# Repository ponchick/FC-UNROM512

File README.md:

# FC-UNROM512

UNROM512 Famicom cartridge PCB (UNROM/UOROM family, extended PRG-ROM bank switching).

Russian version: [`README.ru.md`](README.ru.md)

More details about UNROM512 format and compatibility:

- [NESdev Wiki - UNROM 512](https://www.nesdev.org/wiki/UNROM_512)
- [NESdev Wiki mirror - UNROM 512](https://nesdev-wiki.nes.science/wikipages/UNROM_512.xhtml)

---

## Jumpers (board configuration)

### 1) Flash memory mode (write protection / self-flashing)

| Configuration | `FLASHLOCKED1`-`FLASHLOCKED4` | `FLASHABLE` | 74*139 | Bus conflicts |
| :--- | :---: | :---: | :---: | :---: |
| **Not Flashable** (write-protected) | Closed | Open | Not installed | **Present** |
| **Flashable** (self-flashable) | Open | Closed | Installed | **Absent** |

---

### 2) Mirroring

**Mirroring must match the ROM you are programming.** The game expects a specific mode (vertical/horizontal/1-screen). A wrong setting causes visual glitches.

Only one of these jumpers should be closed. For **Vertical mirroring**, close `VERTICAL` and keep `HORIZONTAL` and `ONE` open.

---

### 3) CHR RAM size configuration (8/16/32 KiB)

**The actual CHR RAM size is defined by the physical RAM chip** (for example, 62256 = 32 KiB). Jumpers only route the required address lines.

| Size | `CHR RAM 8k` | `CHR RAM 8k/16k` | `CHR RAM 16k/32k` | `CHR RAM 32k` |
| :--- | :---: | :---: | :---: | :---: |
| 8 KiB | Closed | Closed | Open | Open |
| 16 KiB | Open | Closed | Closed | Open |
| 32 KiB | Open | Open | Closed | Closed |

> **Use smaller CHR RAM sizes (8/16 KiB) only if the target ROM explicitly supports them.** Most UNROM512 / Mapper 30 software expects 32 KiB. Forcing a smaller size on unsupported ROMs can cause errors.

---

## License

This project is licensed under CERN Open Hardware Licence Version 2 - Permissive (`CERN-OHL-P-2.0`), see `LICENSE`.

SPDX-License-Identifier: `CERN-OHL-P-2.0`

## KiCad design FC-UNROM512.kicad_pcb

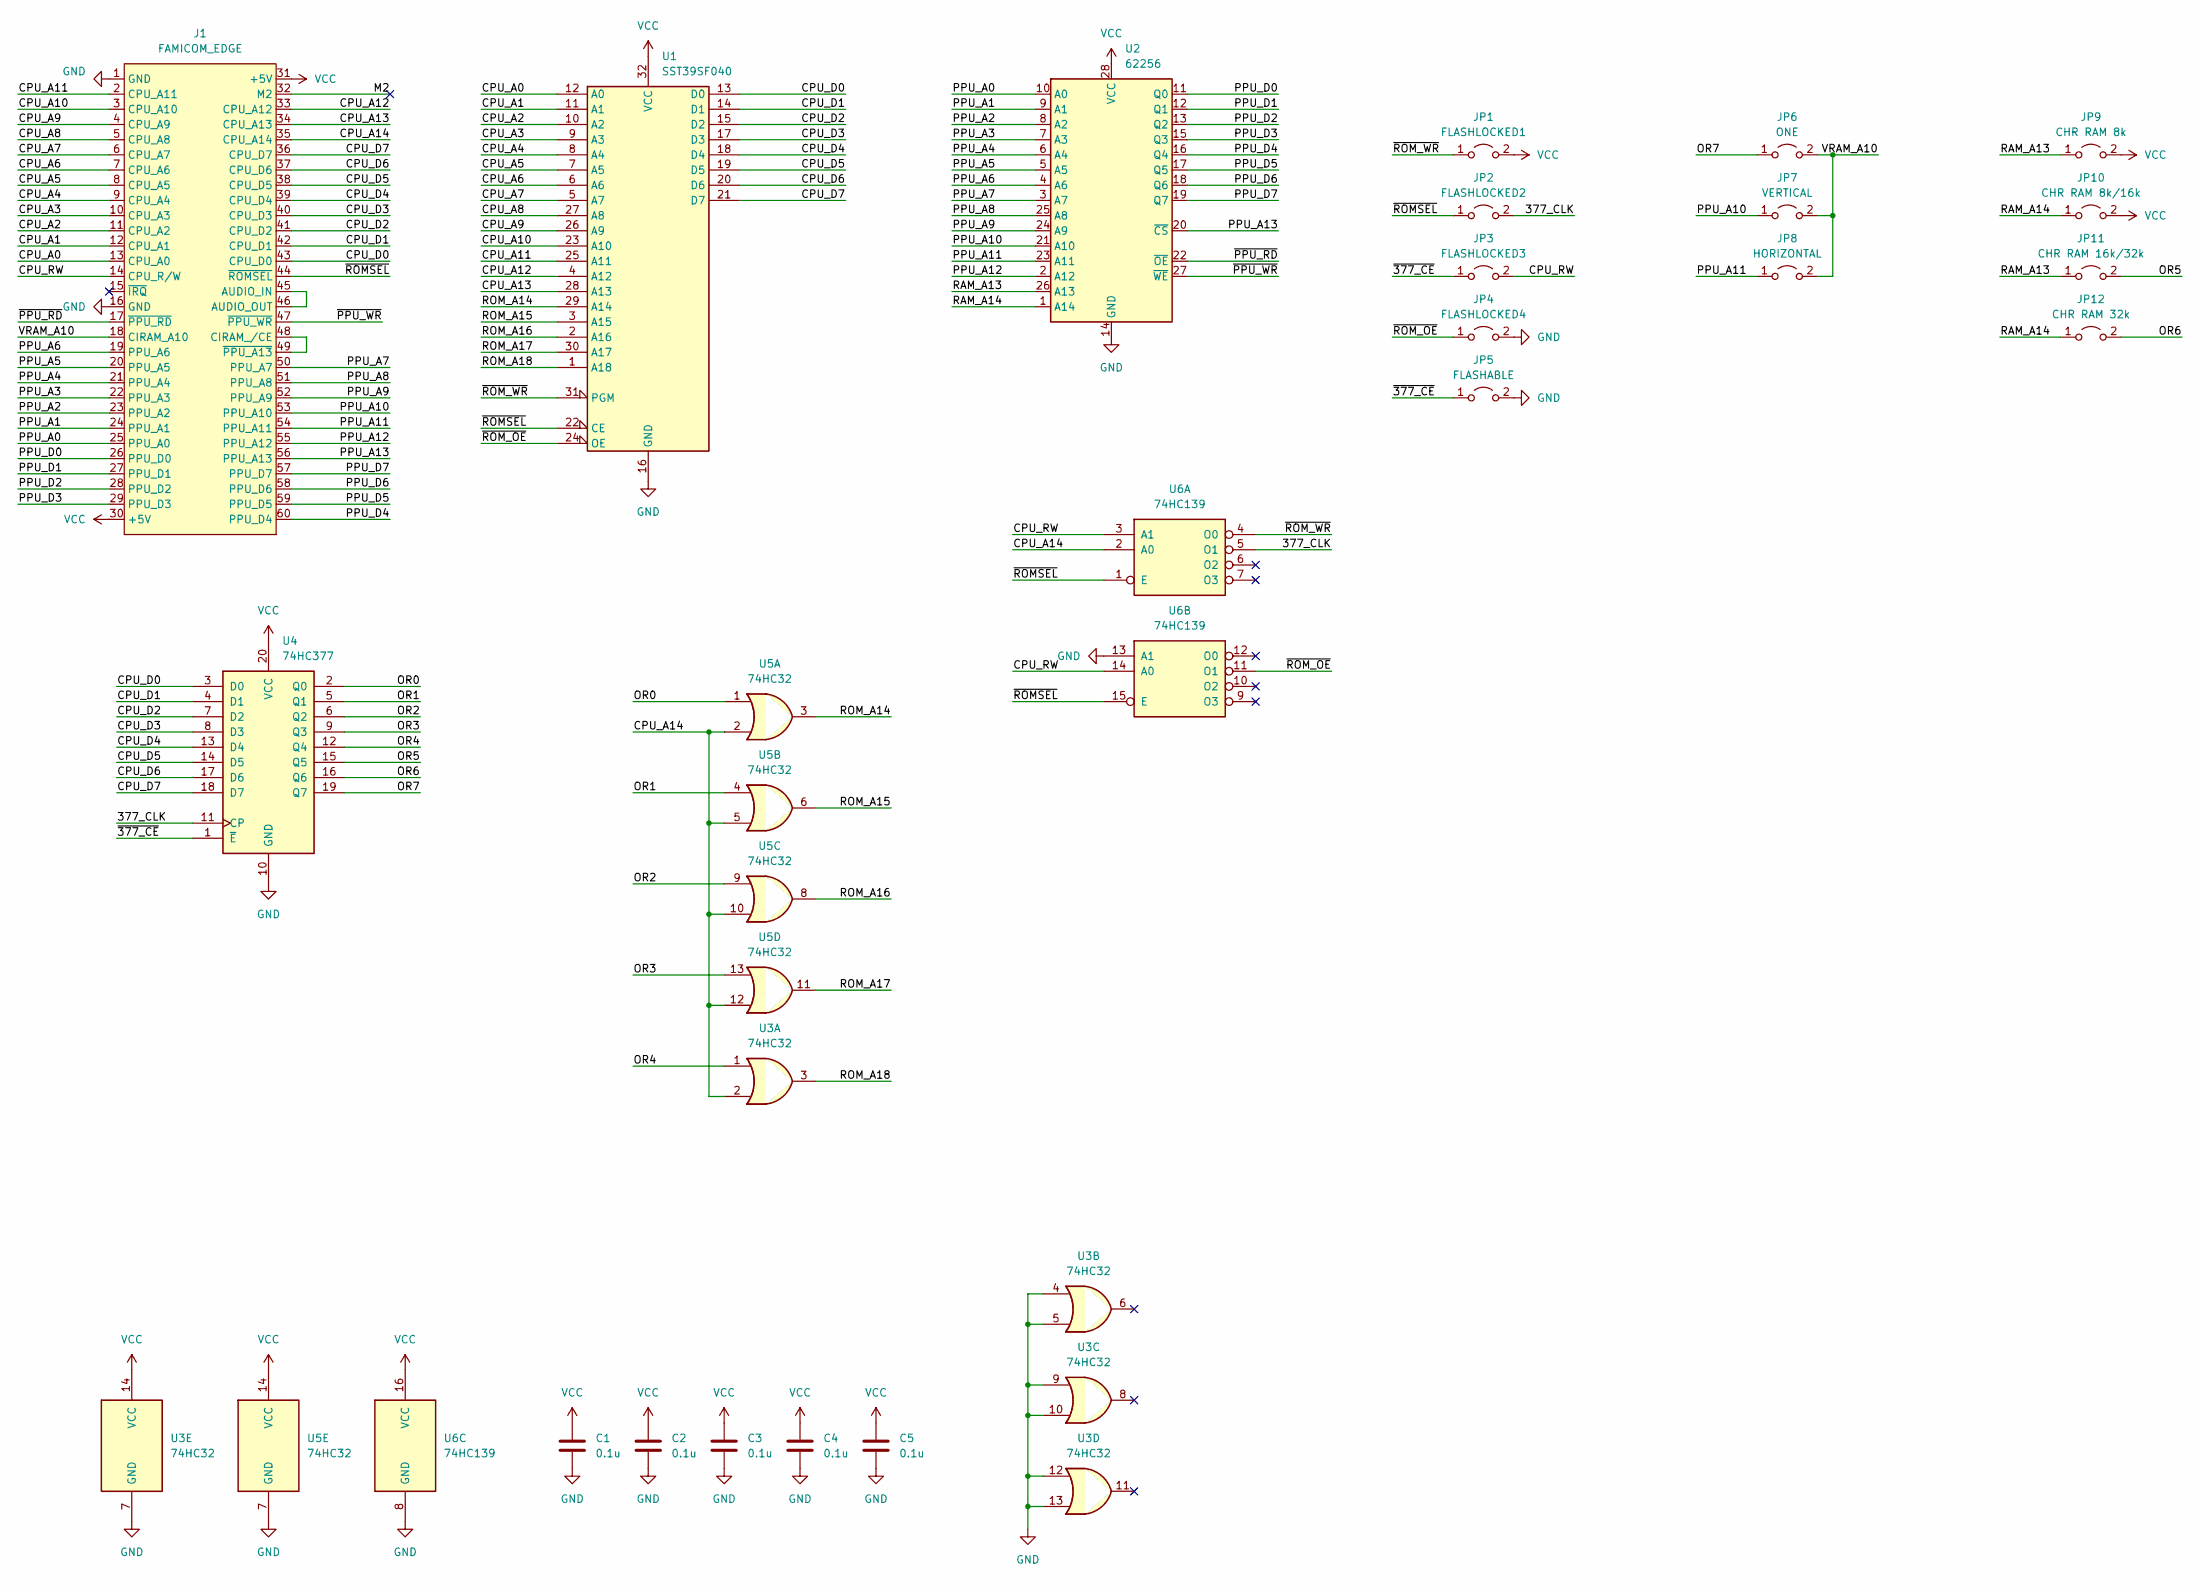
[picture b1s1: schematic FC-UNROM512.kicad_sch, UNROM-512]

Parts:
C1, C2, C3, C4, C5: 0.1u; C_Disc_D4.3mm_W1.9mm_P5.00mm
J1: FAMICOM_EDGE; CONN_EDGE_2x60
JP1: FLASHLOCKED1; SolderJumper-2_P1.3mm_Open_Pad1.0x1.5mm
JP2: FLASHLOCKED2; SolderJumper-2_P1.3mm_Open_Pad1.0x1.5mm
JP3: FLASHLOCKED3; SolderJumper-2_P1.3mm_Open_Pad1.0x1.5mm
JP4: FLASHLOCKED4; SolderJumper-2_P1.3mm_Open_Pad1.0x1.5mm
JP5: FLASHABLE; SolderJumper-2_P1.3mm_Open_Pad1.0x1.5mm
JP6: ONE; SolderJumper-2_P1.3mm_Open_Pad1.0x1.5mm
JP7: VERTICAL; SolderJumper-2_P1.3mm_Open_Pad1.0x1.5mm
JP8: HORIZONTAL; SolderJumper-2_P1.3mm_Open_Pad1.0x1.5mm
JP9: CHR RAM 8k; SolderJumper-2_P1.3mm_Open_Pad1.0x1.5mm
JP10: CHR RAM 8k/16k; SolderJumper-2_P1.3mm_Open_Pad1.0x1.5mm
JP11: CHR RAM 16k/32k; SolderJumper-2_P1.3mm_Open_Pad1.0x1.5mm
JP12: CHR RAM 32k; SolderJumper-2_P1.3mm_Open_Pad1.0x1.5mm
U1: SST39SF040; DIP-32_W15.24mm_Socket
U2: 62256; DIP-28_Dual
U3, U5: 74HC32; DIP-14_W7.62mm
U4: 74HC377; DIP-20_W7.62mm
U6: 74HC139; DIP-16_W7.62mm

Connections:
/377_CLK: JP2.2 (B), U4.11 (CP), U6.5 (O1)
/CPU_A0: J1.13 (CPU_A0), U1.12 (A0)
/CPU_A1: J1.12 (CPU_A1), U1.11 (A1)
/CPU_A2: J1.11 (CPU_A2), U1.10 (A2)
/CPU_A3: J1.10 (CPU_A3), U1.9 (A3)
/CPU_A4: J1.9 (CPU_A4), U1.8 (A4)
/CPU_A5: J1.8 (CPU_A5), U1.7 (A5)
/CPU_A6: J1.7 (CPU_A6), U1.6 (A6)
/CPU_A7: J1.6 (CPU_A7), U1.5 (A7)
/CPU_A8: J1.5 (CPU_A8), U1.27 (A8)
/CPU_A9: J1.4 (CPU_A9), U1.26 (A9)
/CPU_A10: J1.3 (CPU_A10), U1.23 (A10)
/CPU_A11: J1.2 (CPU_A11), U1.25 (A11)
/CPU_A12: J1.33 (CPU_A12), U1.4 (A12)
/CPU_A13: J1.34 (CPU_A13), U1.28 (A13)
/CPU_A14: J1.35 (CPU_A14), U3.2, U5.2, U5.5, U5.10, U5.12, U6.2 (A0)
/CPU_D0: J1.43 (CPU_D0), U1.13 (D0), U4.3 (D0)
/CPU_D1: J1.42 (CPU_D1), U1.14 (D1), U4.4 (D1)
/CPU_D2: J1.41 (CPU_D2), U1.15 (D2), U4.7 (D2)
/CPU_D3: J1.40 (CPU_D3), U1.17 (D3), U4.8 (D3)
/CPU_D4: J1.39 (CPU_D4), U1.18 (D4), U4.13 (D4)
/CPU_D5: J1.38 (CPU_D5), U1.19 (D5), U4.14 (D5)
/CPU_D6: J1.37 (CPU_D6), U1.20 (D6), U4.17 (D6)
/CPU_D7: J1.36 (CPU_D7), U1.21 (D7), U4.18 (D7)
/CPU_RW: J1.14 (CPU_R/W), JP3.2 (B), U6.3 (A1), U6.14 (A0)
/M2: J1.32 (M2)
/OR0: U4.2 (Q0), U5.1
/OR1: U4.5 (Q1), U5.4
/OR2: U4.6 (Q2), U5.9
/OR3: U4.9 (Q3), U5.13
/OR4: U3.1, U4.12 (Q4)
/OR5: JP11.2 (B), U4.15 (Q5)
/OR6: JP12.2 (B), U4.16 (Q6)
/OR7: JP6.1 (A), U4.19 (Q7)
/PPU_A0: J1.25 (PPU_A0), U2.10 (A0)
/PPU_A1: J1.24 (PPU_A1), U2.9 (A1)
/PPU_A2: J1.23 (PPU_A2), U2.8 (A2)
/PPU_A3: J1.22 (PPU_A3), U2.7 (A3)
/PPU_A4: J1.21 (PPU_A4), U2.6 (A4)
/PPU_A5: J1.20 (PPU_A5), U2.5 (A5)
/PPU_A6: J1.19 (PPU_A6), U2.4 (A6)
/PPU_A7: J1.50 (PPU_A7), U2.3 (A7)
/PPU_A8: J1.51 (PPU_A8), U2.25 (A8)
/PPU_A9: J1.52 (PPU_A9), U2.24 (A9)
/PPU_A10: J1.53 (PPU_A10), JP7.1 (A), U2.21 (A10)
/PPU_A11: J1.54 (PPU_A11), JP8.1 (A), U2.23 (A11)
/PPU_A12: J1.55 (PPU_A12), U2.2 (A12)
/PPU_A13: J1.56 (PPU_A13), U2.20 (~CS)
/PPU_D0: J1.26 (PPU_D0), U2.11 (Q0)
/PPU_D1: J1.27 (PPU_D1), U2.12 (Q1)
/PPU_D2: J1.28 (PPU_D2), U2.13 (Q2)
/PPU_D3: J1.29 (PPU_D3), U2.15 (Q3)
/PPU_D4: J1.60 (PPU_D4), U2.16 (Q4)
/PPU_D5: J1.59 (PPU_D5), U2.17 (Q5)
/PPU_D6: J1.58 (PPU_D6), U2.18 (Q6)
/PPU_D7: J1.57 (PPU_D7), U2.19 (Q7)
/RAM_A13: JP9.1 (A), JP11.1 (A), U2.26 (A13)
/RAM_A14: JP10.1 (A), JP12.1 (A), U2.1 (A14)
/ROM_A14: U1.29 (A14), U5.3
/ROM_A15: U1.3 (A15), U5.6
/ROM_A16: U1.2 (A16), U5.8
/ROM_A17: U1.30 (A17), U5.11
/ROM_A18: U1.1 (A18), U3.3
/VRAM_A10: J1.18 (CIRAM_A10), JP6.2 (B), JP7.2 (B), JP8.2 (B)
/~377_CE: JP3.1 (A), JP5.1 (A), U4.1 (~E)
/~PPU_RD: J1.17 (~PPU_RD), U2.22 (~OE)
/~PPU_WR: J1.47 (~PPU_WR), U2.27 (~WE)
/~ROMSEL: J1.44 (~ROMSEL), JP2.1 (A), U1.22 (CE), U6.1 (E), U6.15 (E)
/~ROM_OE: JP4.1 (A), U1.24 (OE), U6.11 (O1)
/~ROM_WR: JP1.1 (A), U1.31 (PGM), U6.4 (O0)
GND: C1.2, C2.2, C3.2, C4.2, C5.2, J1.1 (GND), J1.16 (GND), JP4.2 (B), JP5.2 (B), U1.16 (GND), U2.14 (GND), U3.4, U3.5, U3.7 (GND), U3.9, U3.10, U3.12, U3.13, U4.10 (GND), U5.7 (GND), U6.8 (GND), U6.13 (A1)
unnamed: J1.45 (AUDIO_IN), J1.46 (AUDIO_OUT)
unnamed: J1.48 (CIRAM_/CE), J1.49 (~PPU_A13)
VCC: C1.1, C2.1, C3.1, C4.1, C5.1, J1.30 (+5V), J1.31 (+5V), JP1.2 (B), JP9.2 (B), JP10.2 (B), U1.32 (VCC), U2.28 (VCC), U3.14 (VCC), U4.20 (VCC), U5.14 (VCC), U6.16 (VCC)

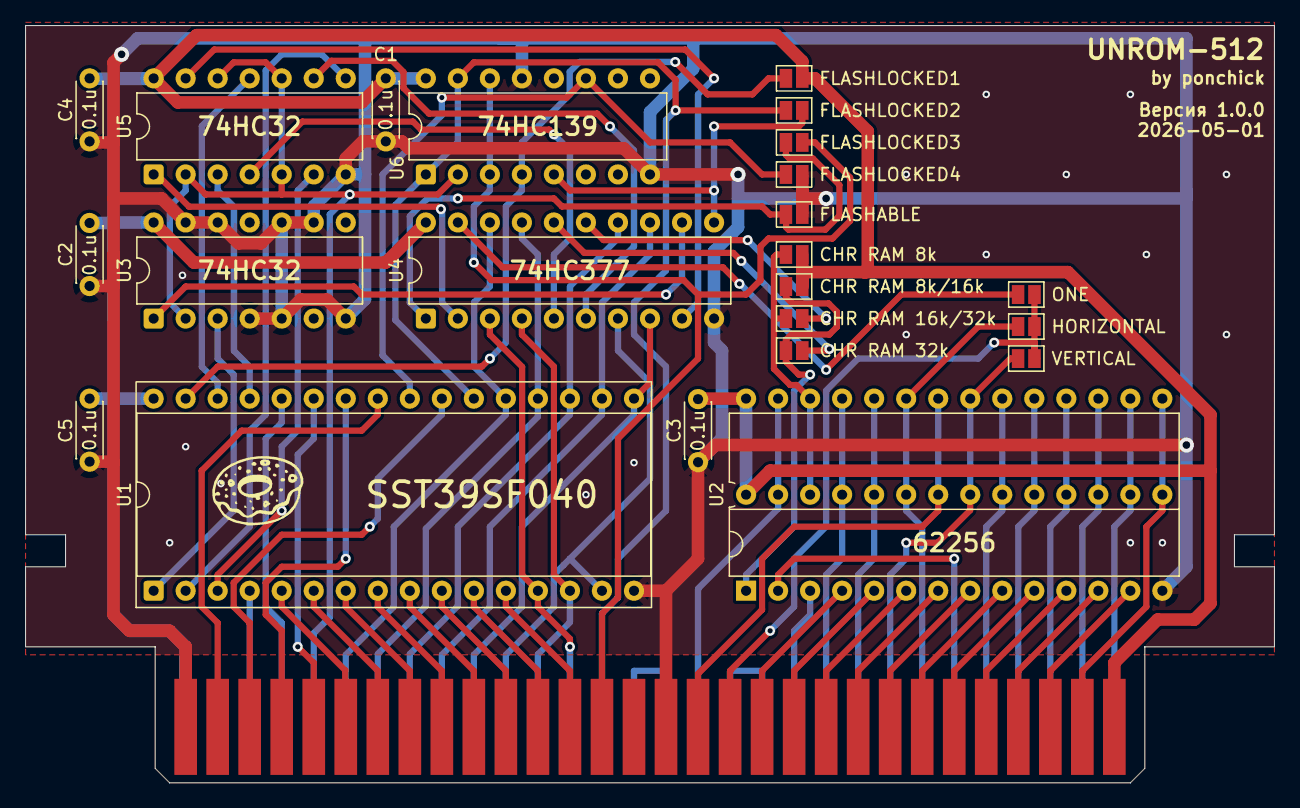
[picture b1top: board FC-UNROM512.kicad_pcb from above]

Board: 2 copper layers, 99.1 x 60.1 mm, 25 parts (0 on the bottom side), 73 nets.

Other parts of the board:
LOGO#: LOGO; ponchick

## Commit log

2026-05-01 Update README files to clarify jumper states for mirroring and correct CHR RAM size configurations.
2026-05-01 Minor PCB update
2026-05-01 Update Russian README
